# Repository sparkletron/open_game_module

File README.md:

# Open Game Module
### Schematic, PCB, and CPLD design.

---

  author: Jay Convertino

  date: 2025.05.21

  details: Open Game Module Expansion for the Coleocvision that is Super Game Module compatible.

  license: MIT

---

## LICENSE
  - All files related to or generated from the KiCAD source fall under the MIT license.
  - All files related to or generated from the Verilog source fall under the MIT license.
  - All files generated by me, Jay Convertino, fall under the MIT license.
  - All files from other sources fall under the license of their specification.

## RELEASE VERSIONS
### Current
  - 1.0.0 - First working version

### Past
  - DEV

## Intro
  This is a open source version of the Super Game Module. This uses a CPLD for the glue logic.

## Documentation
  For detailed usage information, please navigate to one of the following sources. They are the same, just in a different format.
  - [open_game_module.pdf](docs/manual/open_game_module.pdf)
  - [github page](https://sparkletron.github.io/open_game_module/)

## SOFTWARE REQUIREMENTS
  - KiCAD v8.X
  - Quartus v13.0.1sp1 web edition
  - Altera USB Blaster

## BUILD TIPS
  This design is made so anyone can build this. Though it will need a board from a PCB manufacture due to the small pitch and
  vias. There are only a few SMD devices, the CPLD, and a few resistors. These are larger to help make soldering easier.

  Recommend populating the SMD parts first, then moving on to the through hole parts from passive to active.

  All case parts are ABS Plastic.

## Completed Project Image

## PCB IMAGE

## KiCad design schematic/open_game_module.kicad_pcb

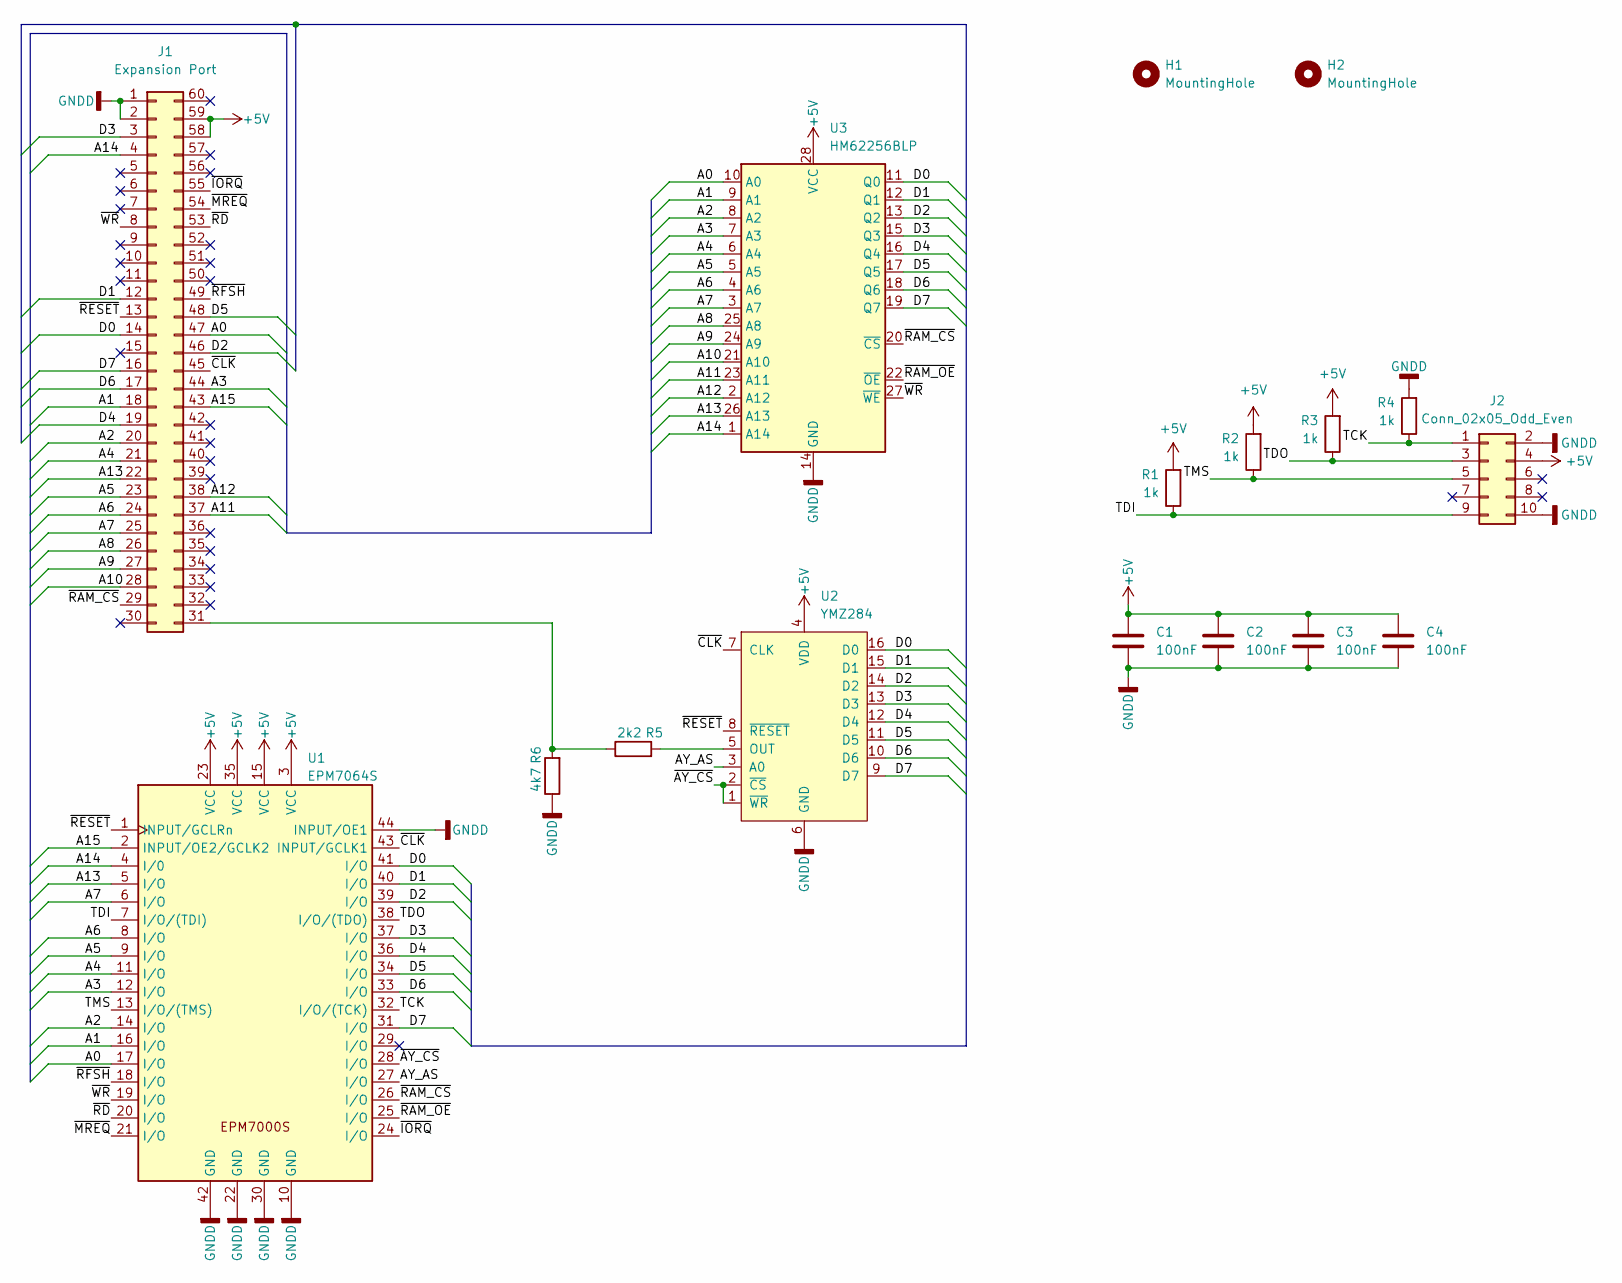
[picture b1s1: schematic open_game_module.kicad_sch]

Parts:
C1, C2, C3, C4: 100nF; C_Disc_D5.0mm_W2.5mm_P5.00mm
H1, H2: MountingHole; MountingHole_2.7mm_M2.5_ISO14580
J1: Expansion Port; Colecovision_Expansion_Mate
J2: Conn_02x05_Odd_Even; PinHeader_2x05_P2.54mm_Vertical
R1, R2, R3, R4: 1k; R_1206_3216Metric_Pad1.30x1.75mm_HandSolder
R5: 2k2; R_Axial_DIN0207_L6.3mm_D2.5mm_P10.16mm_Horizontal
R6: 4k7; R_Axial_DIN0207_L6.3mm_D2.5mm_P10.16mm_Horizontal
U1: EPM7064S; PLCC-44
U2: YMZ284; DIP-16_W7.62mm
U3: HM62256BLP; DIP-28_W15.24mm

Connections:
+5V: C1.1, C2.1, C3.1, C4.1, J1.58, J1.59, J2.4, R1.2, R2.2, R3.2, U1.3 (VCC), U1.15 (VCC), U1.23 (VCC), U1.35 (VCC), U2.4 (VDD), U3.28 (VCC)
/A0: J1.47, U1.17 (I/O), U3.10 (A0)
/A1: J1.18, U1.16 (I/O), U3.9 (A1)
/A2: J1.20, U1.14 (I/O), U3.8 (A2)
/A3: J1.44, U1.12 (I/O), U3.7 (A3)
/A4: J1.21, U1.11 (I/O), U3.6 (A4)
/A5: J1.23, U1.9 (I/O), U3.5 (A5)
/A6: J1.24, U1.8 (I/O), U3.4 (A6)
/A7: J1.25, U1.6 (I/O), U3.3 (A7)
/A8: J1.26, U3.25 (A8)
/A9: J1.27, U3.24 (A9)
/A10: J1.28, U3.21 (A10)
/A11: J1.37, U3.23 (A11)
/A12: J1.38, U3.2 (A12)
/A13: J1.22, U1.5 (I/O), U3.26 (A13)
/A14: J1.4, U1.4 (I/0), U3.1 (A14)
/A15: J1.43, U1.2 (INPUT/OE2/GCLK2)
/AY_AS: U1.27 (I/O), U2.3 (A0)
/D0: J1.14, U1.41 (I/O), U2.16 (D0), U3.11 (Q0)
/D1: J1.12, U1.40 (I/O), U2.15 (D1), U3.12 (Q1)
/D2: J1.46, U1.39 (I/O), U2.14 (D2), U3.13 (Q2)
/D3: J1.3, U1.37 (I/O), U2.13 (D3), U3.15 (Q3)
/D4: J1.19, U1.36 (I/O), U2.12 (D4), U3.16 (Q4)
/D5: J1.48, U1.34 (I/O), U2.11 (D5), U3.17 (Q5)
/D6: J1.17, U1.33 (I/O), U2.10 (D6), U3.18 (Q6)
/D7: J1.16, U1.31 (I/O), U2.9 (D7), U3.19 (Q7)
/TCK: J2.1, R4.1, U1.32 (I/O/(TCK))
/TDI: J2.9, R1.1, U1.7 (I/O/(TDI))
/TDO: J2.3, R3.1, U1.38 (I/O/(TDO))
/TMS: J2.5, R2.1, U1.13 (I/O/(TMS))
/~AY_CS: U1.28 (I/O), U2.1 (~WR), U2.2 (~CS)
/~CLK: J1.45, U1.43 (INPUT/GCLK1), U2.7 (CLK)
/~IORQ: J1.55, U1.24 (I/O)
/~MREQ: J1.54, U1.21 (I/O)
/~RAM_CS: J1.29, U1.26 (I/O), U3.20 (~CS)
/~RAM_OE: U1.25 (I/O), U3.22 (~OE)
/~RD: J1.53, U1.20 (I/O)
/~RESET: J1.13, U1.1 (INPUT/GCLRn), U2.8 (~RESET)
/~RFSH: J1.49, U1.18 (I/O)
/~WR: J1.8, U1.19 (I/O), U3.27 (~WE)
GNDD: C1.2, C2.2, C3.2, C4.2, J1.1, J1.2, J2.2, J2.10, R4.2, R6.1, U1.10 (GND), U1.22 (GND), U1.30 (GND), U1.42 (GND), U1.44 (INPUT/OE1), U2.6 (GND), U3.14 (GND)
unnamed: J1.31, R5.1, R6.2
unnamed: R5.2, U2.5 (OUT)

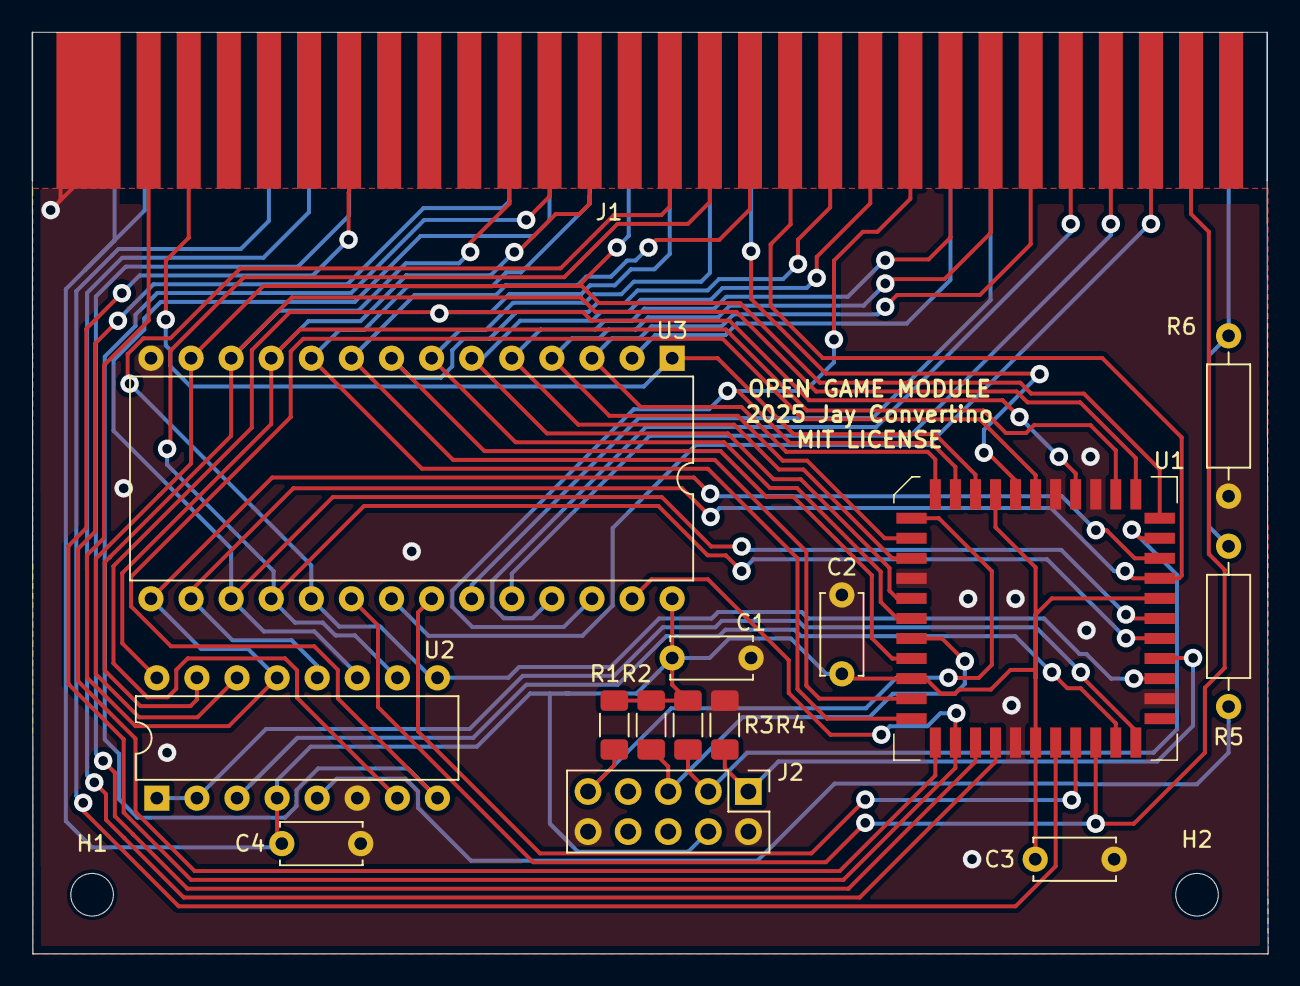
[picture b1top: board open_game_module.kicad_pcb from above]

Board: 2 copper layers, 78.3 x 58.4 mm, 17 parts (0 on the bottom side), 43 nets.

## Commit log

2025-04-20 initial commit, docs incorrect
2025-05-21 added models and pof from quartus
2025-05-22 first initial commit thats actually a draft.. at best:
2025-05-22 update pcb names
2025-05-22 change date
2025-05-22 cleanup docs
2025-05-22 stale backup file
2025-05-24 update docs and 3D model of board
2025-05-24 update 3D case models to be a bit smaller height wise, and emboss OGM SPARKLETRON
2025-05-24 add code hints to docs
2025-05-24 SRAM databook
2025-05-26 update docs with new section
2025-05-27 update documents, improve grammer, remove unneeded stuffs
2025-05-29 update manual with usage images
2025-05-29 update readme image
2025-05-29 update parts listing for new screws
2025-05-29 fixed chip direction
2025-05-30 extra model
2025-06-02 fix resistor for output to 2k2 due to internal sound chip conflict issue
